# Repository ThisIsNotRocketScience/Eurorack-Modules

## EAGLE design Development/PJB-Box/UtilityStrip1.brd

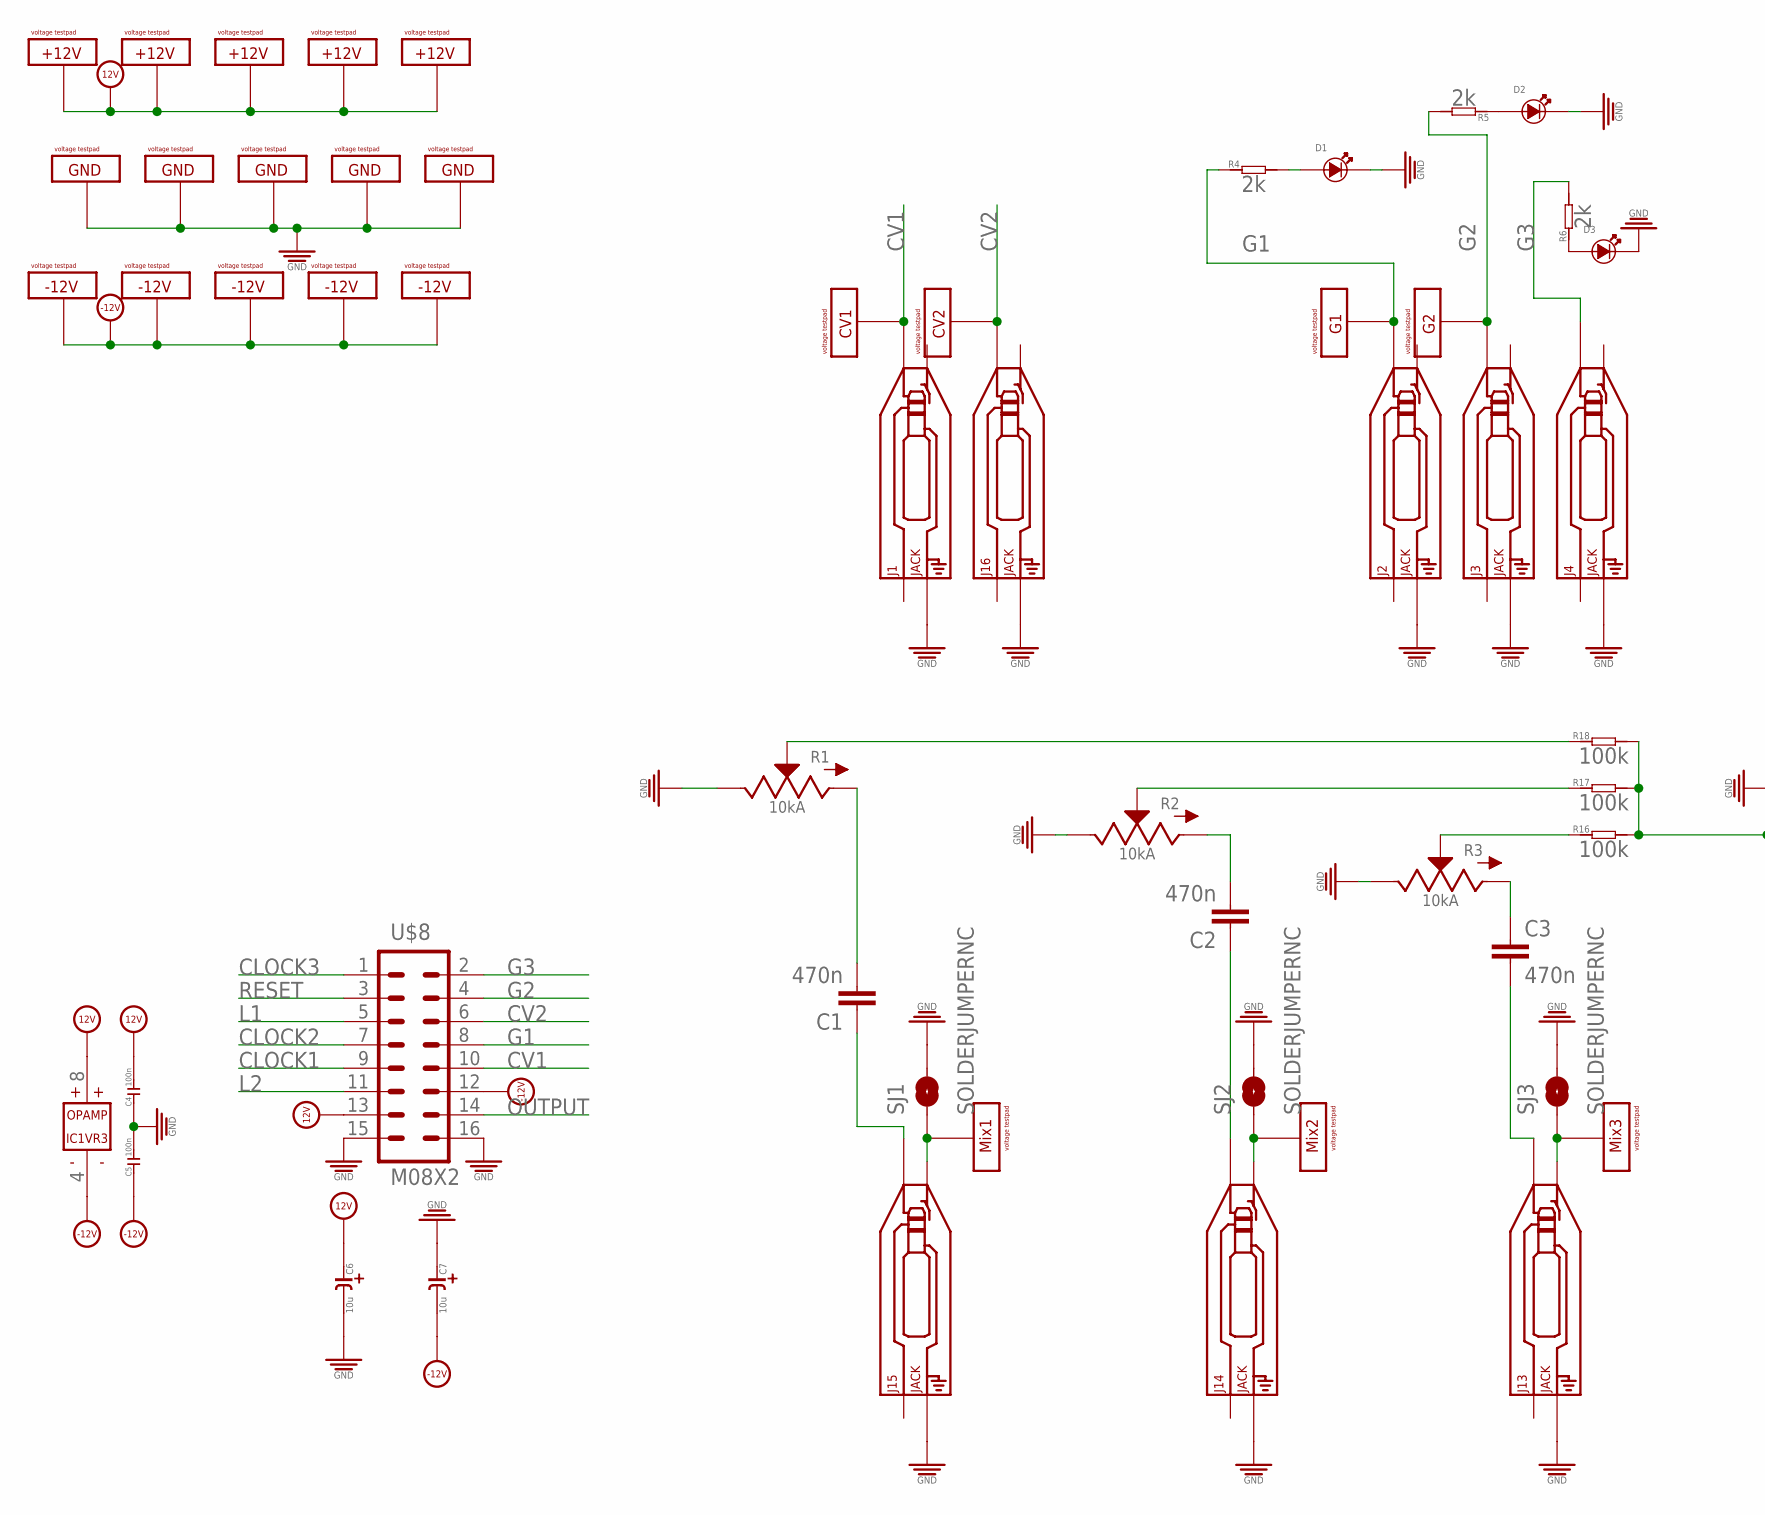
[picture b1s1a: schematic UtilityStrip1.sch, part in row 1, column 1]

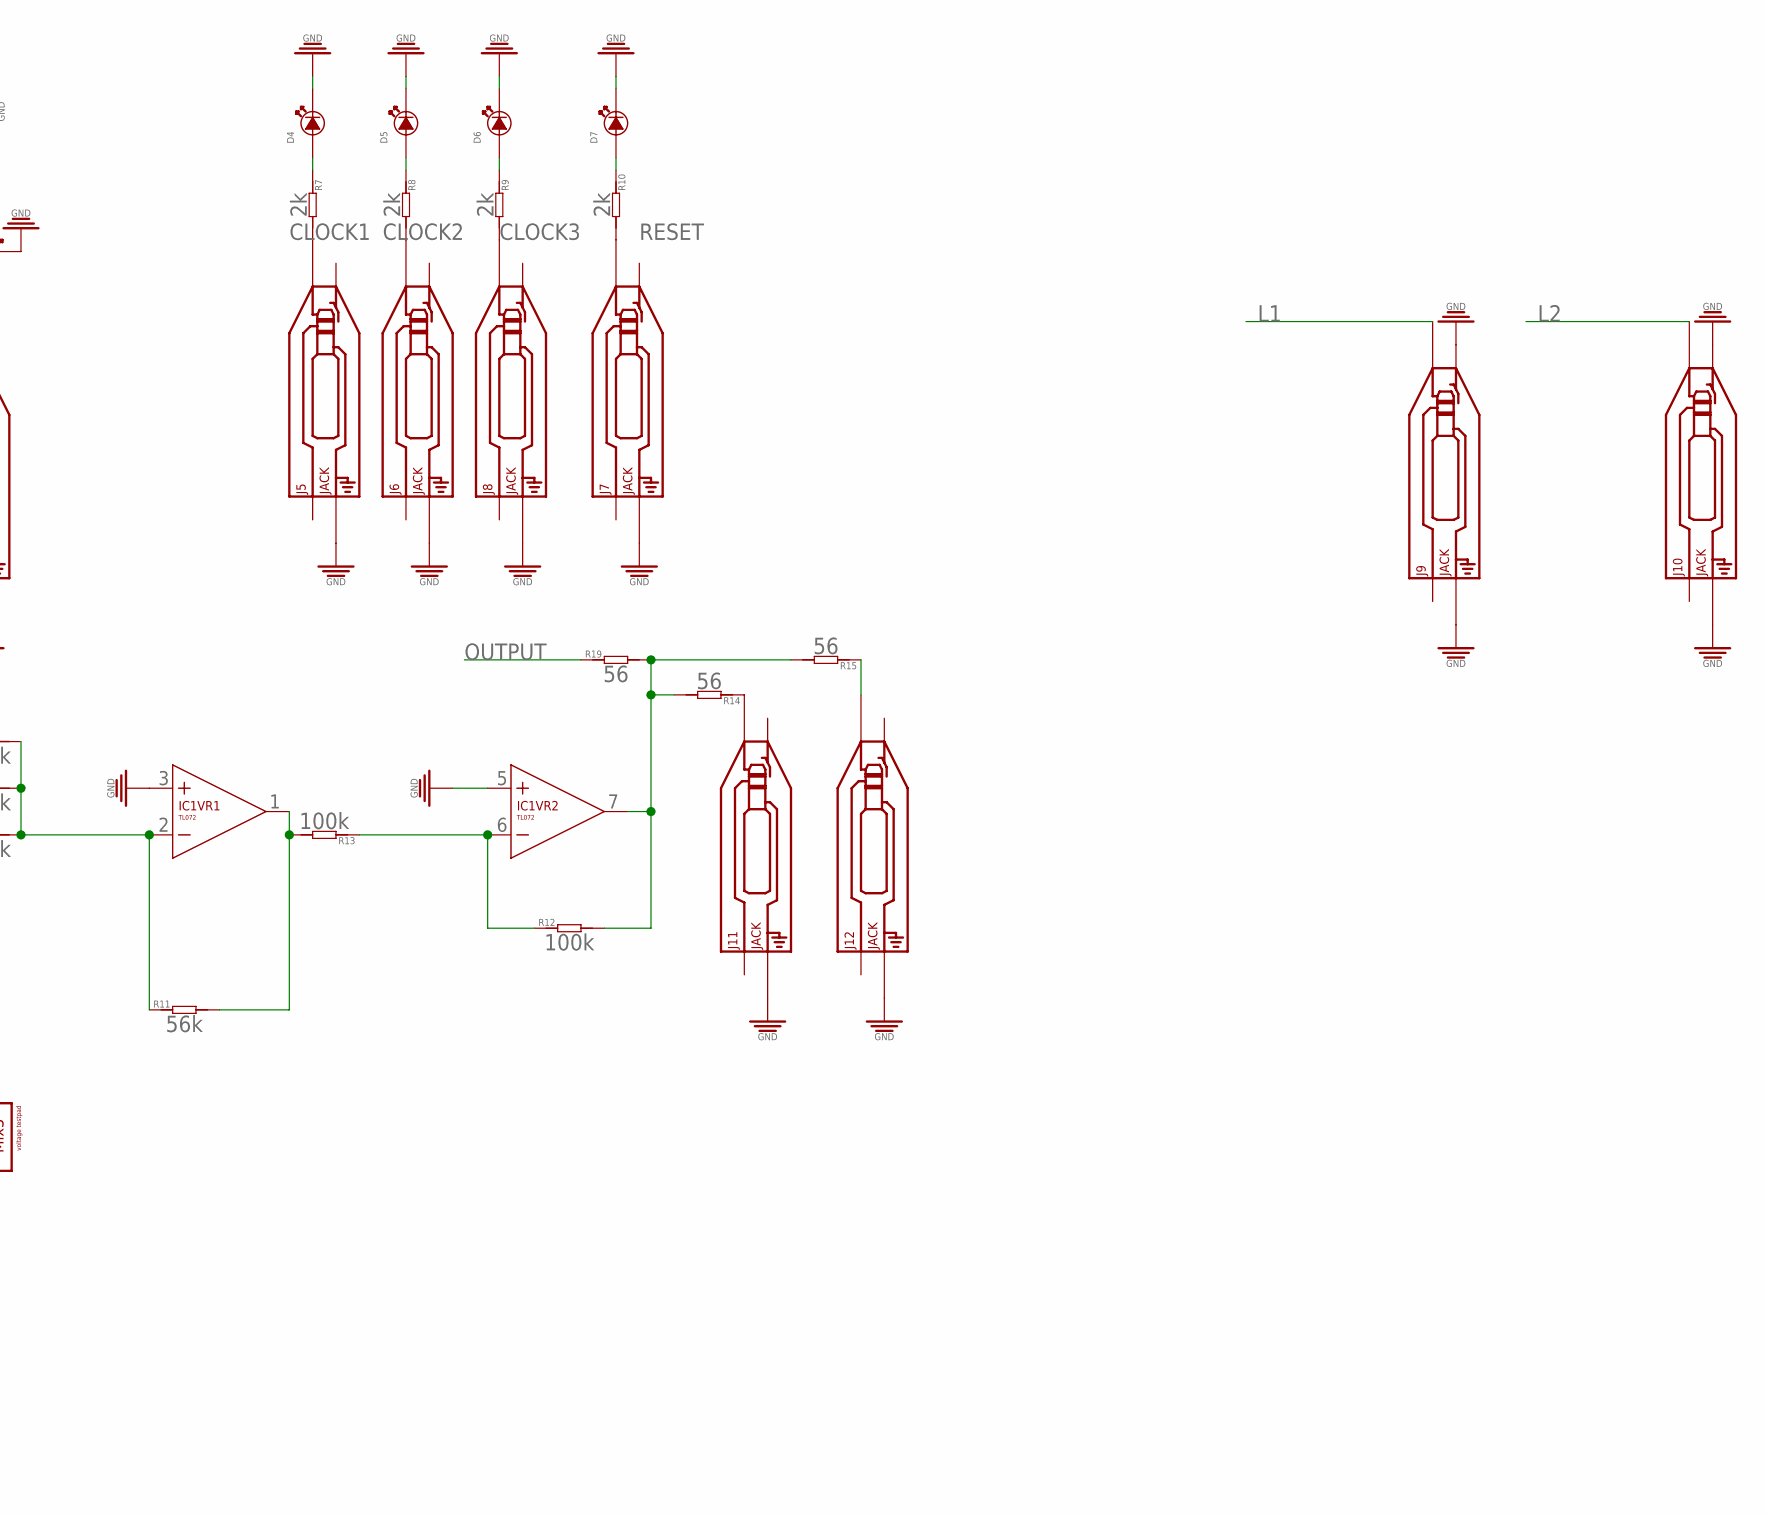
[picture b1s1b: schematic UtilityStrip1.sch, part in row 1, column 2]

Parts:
C1, C2, C3: 470n; C5B4.5
C4, C5: 100n; C0603
C6, C7: 10u; CASE-A_3216
D1, D2, D3, D4, D5, D6, D7: LED3MM; 3MMLED
IC1: TL072; SO08
J1, J2, J3, J4, J5, J6, J7, J8, J9, J10, J11, J12, J13, J14, J15, J16: JACK; 3.5MM-JACK-SWITCH-13MM-NOHOLES
R1, R2, R3: 10kA; ALPS_POT_SQUAREHOLES
R4, R5, R6, R7, R8, R9, R10: 2k; R0603
R11: 56k; R0603
R12, R13, R16, R17, R18: 100k; R0603
R14, R15, R19: 56; R0603
SJ1, SJ2, SJ3: SOLDERJUMPERNC; SJ_2S
U$1, U$2, U$3, U$4, U$5, U$6, U$7, U$9, U$10, U$11, U$12, U$13, U$14, U$15, U$16, U$17, U$18, U$19, U$20, U$21, U$22, U$23: VOLTAGETESTPAD; POWERTESTPAD
U$8: M08X2; 2X8

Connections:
12V: C4.2, C6.+ (1), IC1.8 (V+), U$8.13, U$9.P$1, U$9.P$2, U$9.P$3, U$10.P$1, U$10.P$2, U$10.P$3, U$11.P$1, U$11.P$2, U$11.P$3, U$12.P$1, U$12.P$2, U$12.P$3, U$13.P$1, U$13.P$2, U$13.P$3
-12V: C5.1, C7.- (2), IC1.4 (V-), U$8.12, U$14.P$1, U$14.P$2, U$14.P$3, U$20.P$1, U$20.P$2, U$20.P$3, U$21.P$1, U$21.P$2, U$21.P$3, U$22.P$1, U$22.P$2, U$22.P$3, U$23.P$1, U$23.P$2, U$23.P$3
CLOCK1: J5.TIP_B@1 (TIP), J5.TIP_T@3 (TIP), R7.2, U$8.9
CLOCK2: J6.TIP_B@1 (TIP), J6.TIP_T@3 (TIP), R8.2, U$8.7
CLOCK3: J8.TIP_B@1 (TIP), J8.TIP_T@3 (TIP), R9.2, U$8.1
CV1: J1.TIP_B@1 (TIP), J1.TIP_T@3 (TIP), U$1.P$1, U$1.P$2, U$1.P$3, U$8.10
CV2: J16.TIP_B@1 (TIP), J16.TIP_T@3 (TIP), U$2.P$1, U$2.P$2, U$2.P$3, U$8.6
G1: J2.TIP_B@1 (TIP), J2.TIP_T@3 (TIP), R4.1, U$3.P$1, U$3.P$2, U$3.P$3, U$8.8
G2: J3.TIP_B@1 (TIP), J3.TIP_T@3 (TIP), R5.2, U$4.P$1, U$4.P$2, U$4.P$3, U$8.4
G3: J4.TIP_B@1 (TIP), J4.TIP_T@3 (TIP), R6.2, U$8.2
GND: C4.1, C5.2, C6.- (2), C7.+ (1), D1.-, D2.-, D3.-, D4.-, D5.-, D6.-, D7.-, IC1.3 (+IN), IC1.5 (+IN), J1.RING_B@1 (RING), J1.RING_T@3 (RING), J2.RING_B@1 (RING), J2.RING_T@3 (RING), J3.RING_B@1 (RING), J3.RING_T@3 (RING), J4.RING_B@1 (RING), J4.RING_T@3 (RING), J5.RING_B@1 (RING), J5.RING_T@3 (RING), J6.RING_B@1 (RING), J6.RING_T@3 (RING), J7.RING_B@1 (RING), J7.RING_T@3 (RING), J8.RING_B@1 (RING), J8.RING_T@3 (RING), J9.RING_B@1 (RING), J9.RING_T@3 (RING), J9.SWITCH_B@1 (SWITCH), J9.SWITCH_T@3 (SWITCH), J10.RING_B@1 (RING), J10.RING_T@3 (RING), J10.SWITCH_B@1 (SWITCH), J10.SWITCH_T@3 (SWITCH), J11.RING_B@1 (RING), J11.RING_T@3 (RING), J12.RING_B@1 (RING), J12.RING_T@3 (RING), J13.RING_B@1 (RING), J13.RING_T@3 (RING), J14.RING_B@1 (RING), J14.RING_T@3 (RING), J15.RING_B@1 (RING), J15.RING_T@3 (RING), J16.RING_B@1 (RING), J16.RING_T@3 (RING), R1.P$1 (E), R2.P$1 (E), R3.P$1 (E), SJ1.2, SJ2.2, SJ3.2, U$8.15, U$8.16, U$15.P$1, U$15.P$2, U$15.P$3, U$16.P$1, U$16.P$2, U$16.P$3, U$17.P$1, U$17.P$2, U$17.P$3, U$18.P$1, U$18.P$2, U$18.P$3, U$19.P$1, U$19.P$2, U$19.P$3
L1: J9.TIP_B@1 (TIP), J9.TIP_T@3 (TIP), U$8.5
L2: J10.TIP_B@1 (TIP), J10.TIP_T@3 (TIP), U$8.11
unnamed: C1.2, R1.P$3 (A)
unnamed: C1.1, J15.TIP_B@1 (TIP), J15.TIP_T@3 (TIP)
unnamed: C2.2, R2.P$3 (A)
unnamed: C2.1, J14.TIP_B@1 (TIP), J14.TIP_T@3 (TIP)
unnamed: D4.+, R7.1
unnamed: D5.+, R8.1
unnamed: D6.+, R9.1
unnamed: J15.SWITCH_B@1 (SWITCH), J15.SWITCH_T@3 (SWITCH), SJ1.1, U$5.P$1, U$5.P$2, U$5.P$3
unnamed: J14.SWITCH_B@1 (SWITCH), J14.SWITCH_T@3 (SWITCH), SJ2.1, U$6.P$1, U$6.P$2, U$6.P$3
unnamed: J13.SWITCH_B@1 (SWITCH), J13.SWITCH_T@3 (SWITCH), SJ3.1, U$7.P$1, U$7.P$2, U$7.P$3
unnamed: C3.1, R3.P$3 (A)
unnamed: D1.+, R4.2
unnamed: C3.2, J13.TIP_B@1 (TIP), J13.TIP_T@3 (TIP)
unnamed: D7.+, R10.1
unnamed: D2.+, R5.1
unnamed: D3.+, R6.1
unnamed: J11.TIP_B@1 (TIP), J11.TIP_T@3 (TIP), R14.1
unnamed: J12.TIP_B@1 (TIP), J12.TIP_T@3 (TIP), R15.1
unnamed: IC1.1 (OUT), R11.2, R13.2
unnamed: IC1.6 (-IN), R12.1, R13.1
unnamed: IC1.7 (OUT), R12.2, R14.2, R15.2, R19.2
unnamed: IC1.2 (-IN), R11.1, R16.2, R17.2, R18.2
unnamed: R1.P$2 (S), R18.1
unnamed: R2.P$2 (S), R17.1
unnamed: R3.P$2 (S), R16.1
OUTPUT: R19.1, U$8.14
RESET: J7.TIP_B@1 (TIP), J7.TIP_T@3 (TIP), R10.2, U$8.3

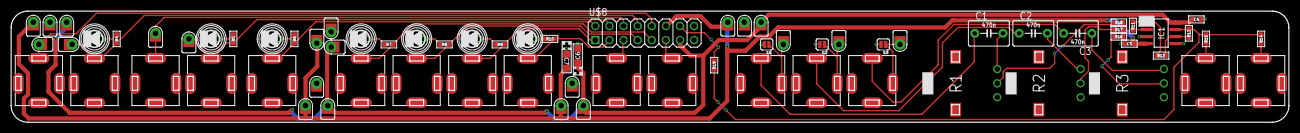
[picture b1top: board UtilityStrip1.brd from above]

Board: 2 copper layers, 230.0 x 20.0 mm, 76 parts (0 on the bottom side), 40 nets.

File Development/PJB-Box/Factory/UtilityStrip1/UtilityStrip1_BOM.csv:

Comment,Designator,Footprint,LCSC Part #,combinedname,name
10kA,"R1, R2, R3",ALPS_POT_SQUAREHOLES,,POT_ALPS_POT_SQUAREHOLES_10kA,POT
JACK,"J1, J2, J3, J4, J5, J6, J7, J8, J9, J10, J11, J12, J13, J14, J15, J16",3.5MM-JACK-SWITCH-13MM-NOHOLES,,AUDIO-JACK_SMALLSYMBOL_3.5MM-JACK-SWITCH-13MM-NOHOLES_JACK,AUDIO-JACK_SMALLSYMBOL
,"D1, D2, D3, D4, D5, D6, D7",3MMLED,,LED*_3MMLED_,LED*
VOLTAGETESTPAD,"U$1, U$2, U$3, U$4, U$5, U$6, U$7, U$9, U$10, U$11, U$12, U$13, U$14, U$15, U$16, U$17, U$18, U$19, U$20, U$21, U$22, U$23",POWERTESTPAD,,VOLTAGETESTPAD_POWERTESTPAD_VOLTAGETESTPAD,VOLTAGETESTPAD
M08X2,"U$8",2X8,,M08X2_2X8_M08X2,M08X2
SOLDERJUMPERNC,"SJ1, SJ2, SJ3",SJ_2S,,SOLDERJUMPER_SJ_2S_SOLDERJUMPERNC,SOLDERJUMPER
2k,"R4, R5, R6, R7, R8, R9, R10",R0603,,R*_R0603_2k,R*
56k,"R11",R0603,,R*_R0603_56k,R*
100k,"R12, R13, R16, R17, R18",R0603,,R*_R0603_100k,R*
56,"R14, R15, R19",R0603,,R*_R0603_56,R*
470n,"C3, C1, C2",C5B4.5,,C_C5B4.5_470n,C
TL072,"IC1",SO08,,TL072_SO08_TL072,TL072
100n,"C4, C5",C0603,,C*_C0603_100n,C*
10u,"C6, C7",CASE-A_3216,,C-POLAR*_CASE-A_3216_10u,C-POLAR*

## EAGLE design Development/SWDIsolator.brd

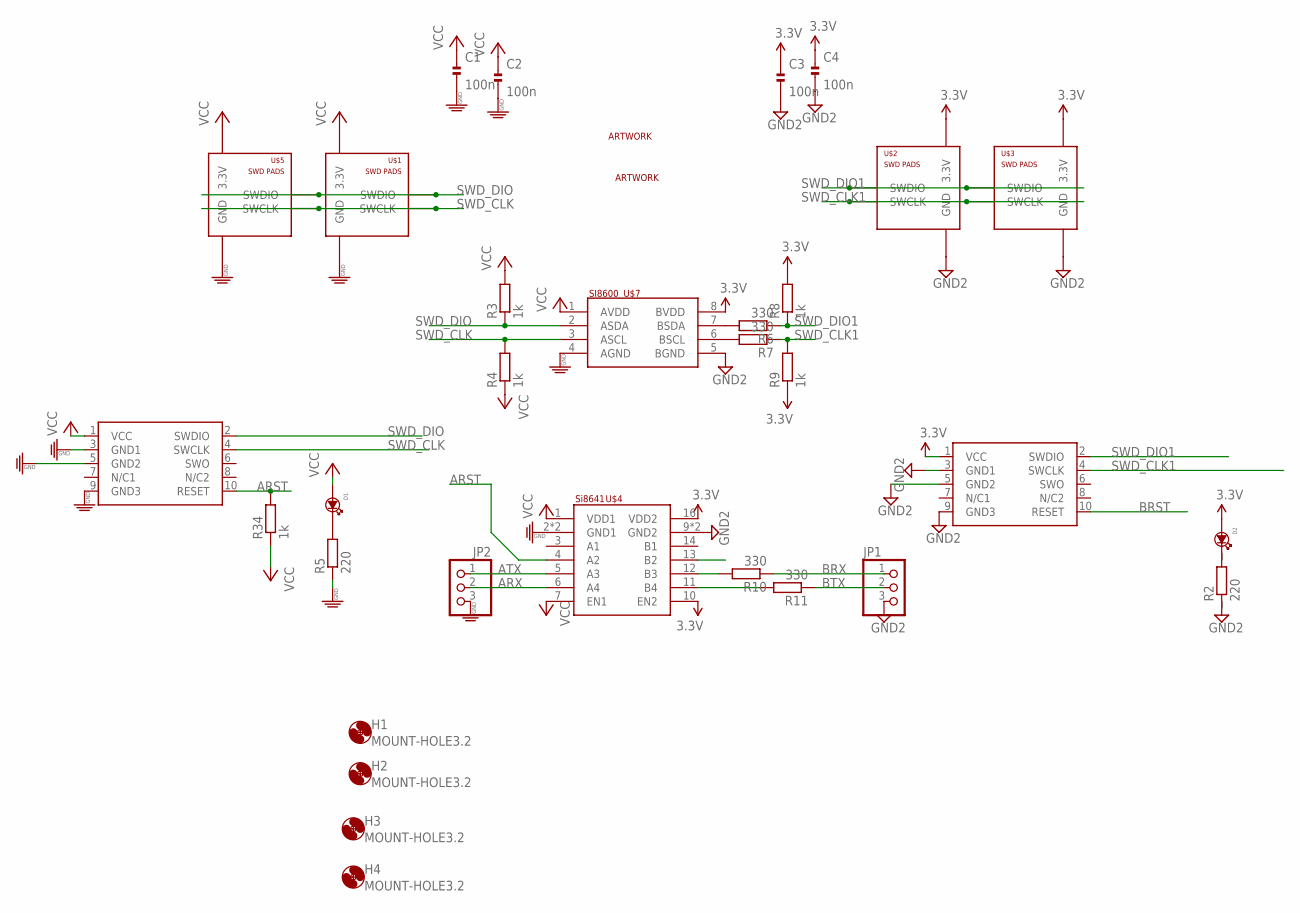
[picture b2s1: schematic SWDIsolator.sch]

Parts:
C1, C2, C3, C4: 100n; C0402
D1, D2: LED; LED0603
H1, H2, H3, H4: MOUNT-HOLE3.2; 3,2
JP1, JP2: PINHD-1X3CB; 1X03-CLEANBIG
R2, R5: 220; R0402
R3, R4, R8, R9, R34: 1k; R0402
R6, R7, R10, R11: 330; R0402
SWD1, SWD2: CORTEX_SWD; M50-3600542
U$1, U$2: SWD_PADS; SWDPADS
U$3, U$5: SWD_PADS_NOTITLE; SWDPADS_NOTITLE
U$4: SI8641; SO16
U$6: TINRS_ARTWORKLOGO; TINRSLOGO
U$7: SI8600AB; SO8
U$8: TINRS_ARTWORKROCKET; TINRS_ROCKET

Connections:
3.3V: C3.1, C4.1, D2.+, R8.2, R9.1, SWD2.1 (VCC), U$2.3.3V, U$3.3.3V, U$4.10 (EN2), U$4.16 (VDD2), U$7.8 (BVDD)
ARST: R34.2, SWD1.10 (RESET), U$4.4 (A2)
ARX: JP2.2, U$4.6 (A4)
ATX: JP2.1, U$4.5 (A3)
BRST: SWD2.10 (RESET), U$4.13 (B2)
BRX: JP1.1, R10.1
BTX: JP1.2, R11.1
GND: C1.2, C2.2, JP2.3, R5.1, SWD1.3 (GND1), SWD1.5 (GND2), SWD1.9 (GND3), U$1.GND, U$4.2 (GND1), U$4.8 (GND1), U$5.GND, U$7.4 (AGND)
GND2: C3.2, C4.2, JP1.3, R2.1, SWD2.3 (GND1), SWD2.5 (GND2), SWD2.9 (GND3), U$2.GND, U$3.GND, U$4.9 (GND2), U$4.15 (GND2), U$7.5 (BGND)
unnamed: R6.2, U$7.7 (BSDA)
unnamed: D1.-, R5.2
unnamed: D2.-, R2.2
unnamed: R7.2, U$7.6 (BSCL)
unnamed: R10.2, U$4.12 (B3)
unnamed: R11.2, U$4.11 (B4)
SWD_CLK: R4.2, SWD1.4 (SWCLK), U$1.SWCLK, U$5.SWCLK, U$7.3 (ASCL)
SWD_CLK1: R7.1, R9.2, SWD2.4 (SWCLK), U$2.SWCLK, U$3.SWCLK
SWD_DIO: R3.1, SWD1.2 (SWDIO), U$1.SWDIO, U$5.SWDIO, U$7.2 (ASDA)
SWD_DIO1: R6.1, R8.1, SWD2.2 (SWDIO), U$2.SWDIO, U$3.SWDIO
VCC: C1.1, C2.1, D1.+, R3.2, R4.1, R34.1, SWD1.1 (VCC), U$1.3.3V, U$4.1 (VDD1), U$4.7 (EN1), U$5.3.3V, U$7.1 (AVDD)

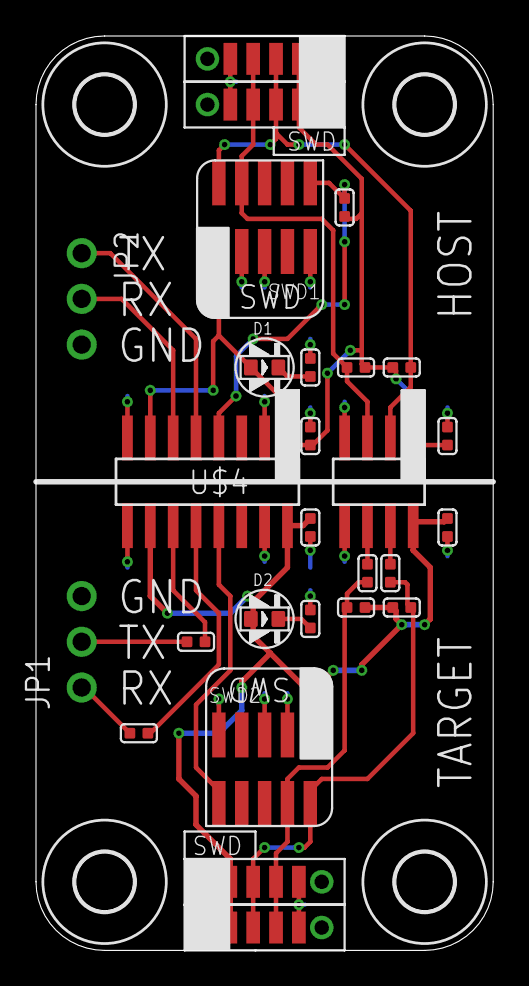
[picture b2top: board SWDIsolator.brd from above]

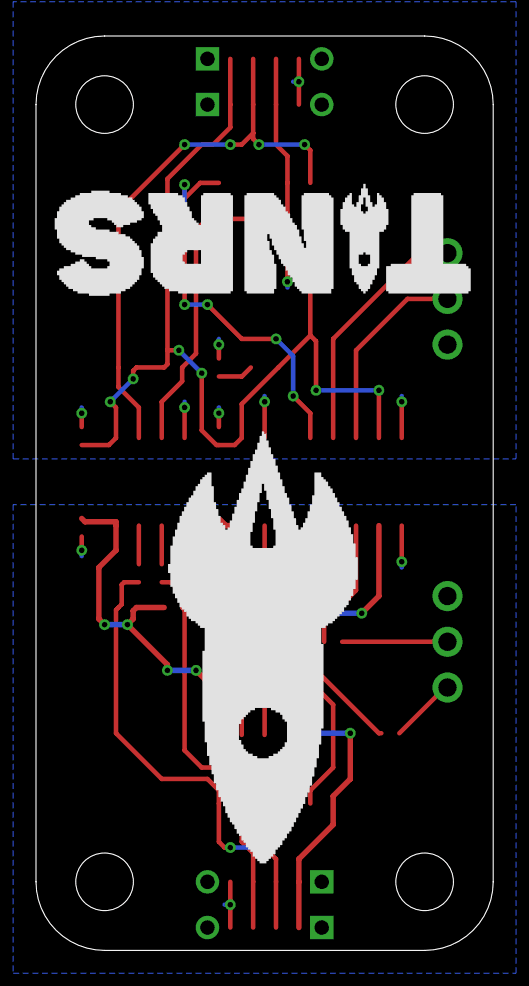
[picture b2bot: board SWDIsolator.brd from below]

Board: 2 copper layers, 25.4 x 50.8 mm, 33 parts (2 on the bottom side), 20 nets.

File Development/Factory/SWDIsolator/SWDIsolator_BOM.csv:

Comment,Designator,Footprint,LCSC Part #,combinedname,name
,"D1, D2",LED0603,,LED*_LED0603_,LED*
220,"R2, R5",R0402,,R-EU__R0402_220,R-EU_
1k,"R34, R3, R4, R8, R9",R0402,,R-EU__R0402_1k,R-EU_
330,"R6, R7, R10, R11",R0402,,R-EU__R0402_330,R-EU_
CORTEX_SWD,"SWD1, SWD2",M50-3600542,,CORTEX_SWD_M50-3600542_CORTEX_SWD,CORTEX_SWD
SWD_PADS,"U$1, U$2",SWDPADS,,SWD_PADS_SWDPADS_SWD_PADS,SWD_PADS
SWD_PADS_NOTITLE,"U$3, U$5",SWDPADS_NOTITLE,,SWD_PADS_SWDPADS_NOTITLE_SWD_PADS_NOTITLE,SWD_PADS
SI8600AB,"U$7",SO8,,SI8600_SO8_SI8600AB,SI8600
100n,"C1, C2, C3, C4",C0402,,C-EU_C0402_100n,C-EU
SI8641,"U$4",SO16,,SI8641_SO16_SI8641,SI8641
,"JP1, JP2",1X03-CLEANBIG,,PINHD-1X3_1X03-CLEANBIG_,PINHD-1X3
MOUNT-HOLE3.2,"H1, H2, H3, H4",3,2,,MOUNT-HOLE_3.2_MOUNT-HOLE3.2,MOUNT-HOLE
TINRS_ARTWORKLOGO,"U$6",TINRSLOGO,,TINRS_ARTWORK_TINRSLOGO_TINRS_ARTWORKLOGO,TINRS_ARTWORK
TINRS_ARTWORKROCKET,"U$8",TINRS_ROCKET,,TINRS_ARTWORK_TINRS_ROCKET_TINRS_ARTWORKROCKET,TINRS_ARTWORK

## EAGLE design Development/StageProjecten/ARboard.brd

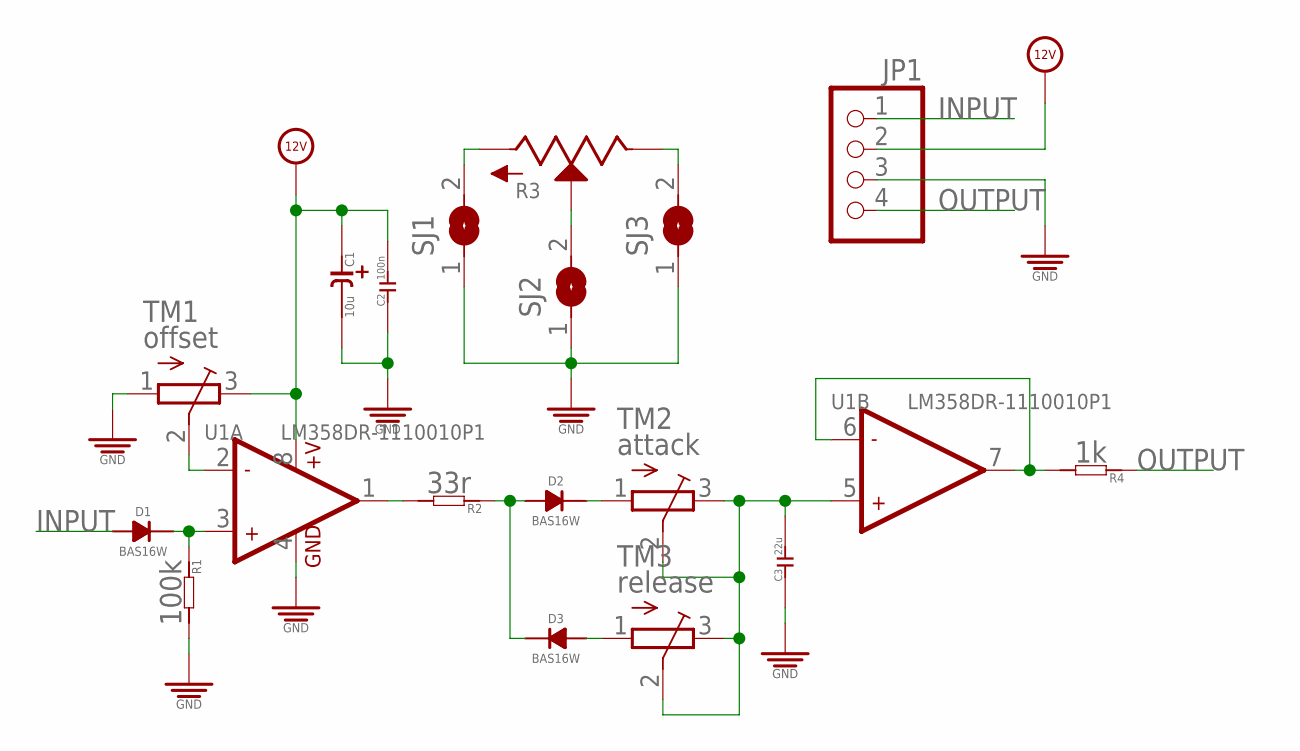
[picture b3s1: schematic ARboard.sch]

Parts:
C1: 10u; CASE-A_3216
C2: 100n; C0603
C3: 22u; C0603
D1, D2, D3: BAS16W; SOT-323
JP1: PINHD-1X4; 1X04
R1: 100k; R0603
R2: 33r; R0603
R3: POTSQUAREHOLE_SMALLKNOB; ALPS_POT_SQUAREHOLES
R4: 1k; R0603
SJ1, SJ2, SJ3: SJ
TM1: offset; TC33X
TM2: attack; TC33X
TM3: release; TC33X
U1: LM358DR-1110010P1; SOIC8

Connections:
12V: C1.+ (1), C2.2, JP1.2, TM1.3 (E), U1.8 (+V)
GND: C1.- (2), C2.1, C3.1, JP1.3, R1.2, SJ1.1, SJ2.1, SJ3.1, TM1.1 (A), U1.4 (GND)
INPUT: D1.ANODE, JP1.1
unnamed: R3.P$3 (A), SJ1.2
unnamed: D2.ANODE, D3.CATHODE, R2.1
unnamed: D3.ANODE, TM3.1 (A)
unnamed: D2.CATHODE, TM2.1 (A)
unnamed: R2.2, U1.1 (OUT1)
unnamed: TM1.2 (S), U1.2 (-IN1)
unnamed: D1.CATHODE, R1.1, U1.3 (+IN1)
unnamed: C3.2, TM2.2 (S), TM2.3 (E), TM3.2 (S), TM3.3 (E), U1.5 (+IN2)
unnamed: R4.2, U1.6 (-IN2), U1.7 (OUT2)
unnamed: R3.P$2 (S), SJ2.2
unnamed: R3.P$1 (E), SJ3.2
OUTPUT: JP1.4, R4.1

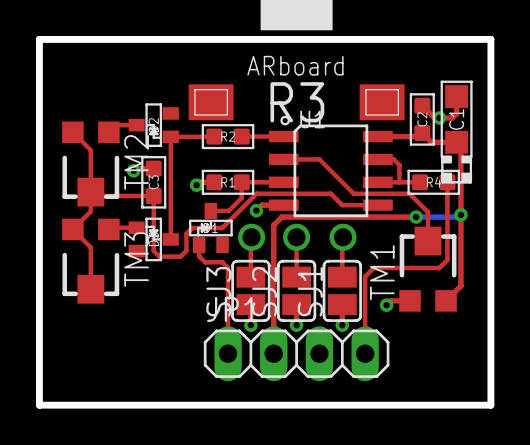
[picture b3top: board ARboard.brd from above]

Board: 2 copper layers, 25.1 x 20.3 mm, 18 parts (0 on the bottom side), 15 nets.

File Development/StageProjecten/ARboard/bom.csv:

Qty,Designator,Footprint,Comment
1,JP1,1X04,
1,R3,ALPS_POT_SQUAREHOLES,
3,"SJ1, SJ2, SJ3",SJ,
1,R1,R0603,100k
1,C2,C0603,100n
1,C1,CASE-A_3216,10u
1,R4,R0603,1k
1,C3,C0603,22u
1,R2,R0603,33r
3,"D1, D2, D3",SOT-323,BAS16W
1,U1,SOIC8,LM358DR-1110010P1
1,TM2,TC33X,attack
1,TM1,TC33X,offset
1,TM3,TC33X,release

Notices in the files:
parts and their libraries:
SparkFun-Connectors: Licensing: CC v3.0 Share-Alike You are welcome to use this library for commercial purposes.
